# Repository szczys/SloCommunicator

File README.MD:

SloCommunicator
======

Communicator watch built for 2016 Bring-a-Hack (end of Bay Area Maker Faire Weekend).

This is based on the stalled [SloJak](https://github.com/szczys/SloJak) project. It is a 128x64 OLED screen with a rotary encoder and two buttons (actually 3 with encoder click but that's not designed into the board artwork).

Two things prevent this watch from communicating: I would need a second one to communicate with, and I didn't include the 900 MHz radio module in the design. This is just a quick and dirty built.

To make up for the lack of actual communications I will write KnobSnake, a classic game of snake that's played only by spinning the rotary encoder knob.

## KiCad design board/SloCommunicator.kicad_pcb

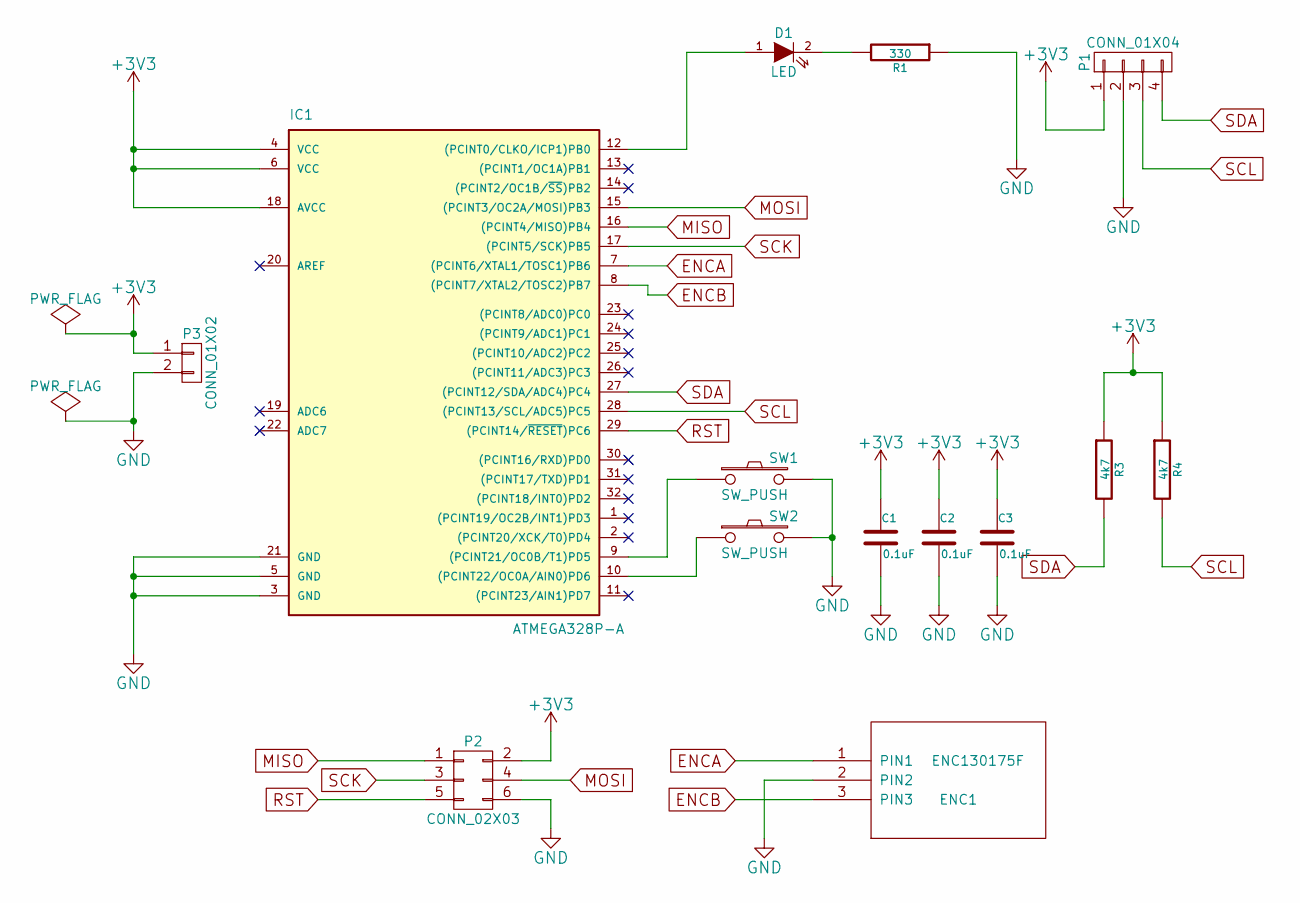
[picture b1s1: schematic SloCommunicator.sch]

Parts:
C1, C2, C3: 0.1uF; C_0805
D1: LED; LED_0805
ENC1: ENC130175F; enc130175f
IC1: ATMEGA328P-A; TQFP-32_7x7mm_Pitch0.8mm
P1: CONN_01X04; Pin_Header_Straight_1x04
P2: CONN_02X03; Pin_Header_Straight_2x03
P3: CONN_01X02; Pin_Header_Straight_1x02
R1: 330; R_0805
R3, R4: 4k7; R_0805
SW1, SW2: SW_PUSH; TACT_SMALL

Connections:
+3V3: C1.1, C2.1, C3.1, IC1.4 (VCC), IC1.6 (VCC), IC1.18 (AVCC), P1.1, P2.2, P3.1, R3.1, R4.1
ENCA: ENC1.1 (PIN1), IC1.7 ((PCINT6/XTAL1/TOSC1)PB6)
ENCB: ENC1.3 (PIN3), IC1.8 ((PCINT7/XTAL2/TOSC2)PB7)
GND: C1.2, C2.2, C3.2, ENC1.2 (PIN2), IC1.3 (GND), IC1.5 (GND), IC1.21 (GND), P1.2, P2.6, P3.2, R1.1, SW1.2, SW2.2
MISO: IC1.16 ((PCINT4/MISO)PB4), P2.1
MOSI: IC1.15 ((PCINT3/OC2A/MOSI)PB3), P2.4
unnamed: D1.1 (A), IC1.12 ((PCINT0/CLKO/ICP1)PB0)
unnamed: D1.2 (K), R1.2
unnamed: IC1.9 ((PCINT21/OC0B/T1)PD5), SW1.1
unnamed: IC1.10 ((PCINT22/OC0A/AIN0)PD6), SW2.1
RST: IC1.29 ((PCINT14/~RESET~)PC6), P2.5
SCK: IC1.17 ((PCINT5/SCK)PB5), P2.3
SCL: IC1.28 ((PCINT13/SCL/ADC5)PC5), P1.3, R4.2
SDA: IC1.27 ((PCINT12/SDA/ADC4)PC4), P1.4, R3.2

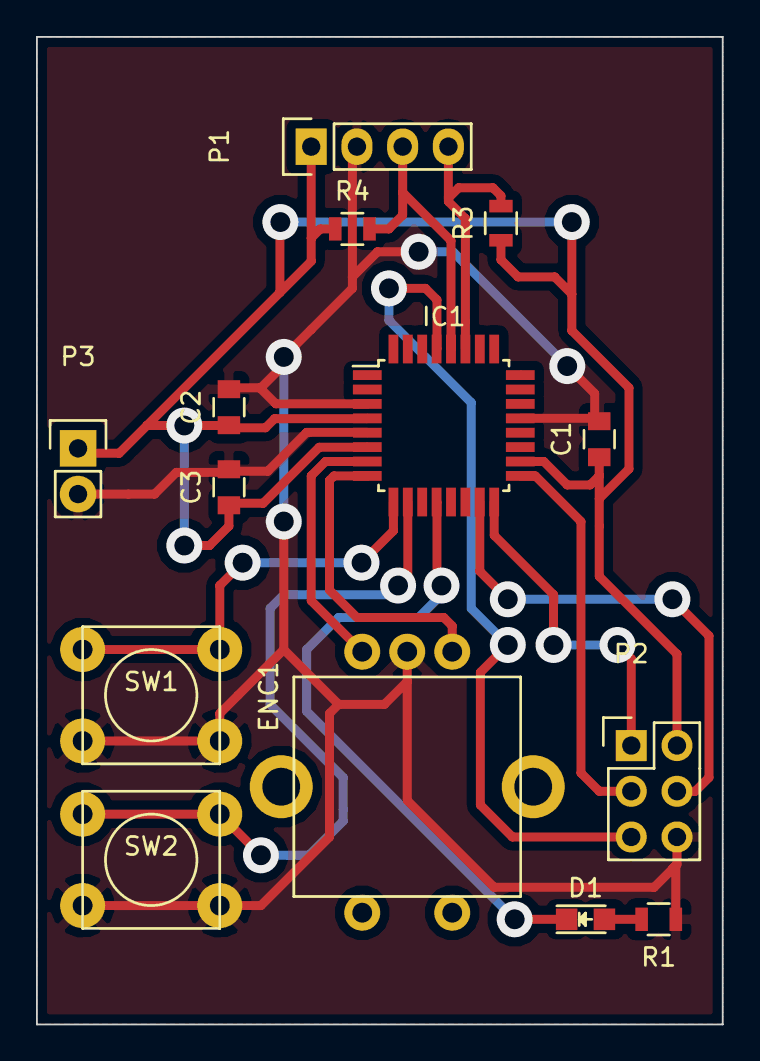
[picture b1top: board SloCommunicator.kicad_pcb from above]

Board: 2 copper layers, 38.1 x 54.9 mm, 14 parts (0 on the bottom side), 14 nets.

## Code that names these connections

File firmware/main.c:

/********************************
* SloJak                    	*
* MIT License               	*
* Copyright 2015 - Mike Szczys  *
* http://jumptuck.com 	    	*
*				                *
********************************/

#define F_CPU 8000000

#include <avr/io.h>
#include <avr/interrupt.h>
#include <avr/pgmspace.h>
#include <util/delay.h>

#include "menu.h"
#include "oledControl.h"
#include "game.h"


/************** Setup a rotary encoder ********************/
/* Atmega168 */
/* encoder port */
#define ENC_CTL	DDRB	//encoder port control
#define ENC_WR	PORTB	//encoder port write
#define ENC_RD	PINB	//encoder port read
#define ENC_A 6
#define ENC_B 7

volatile int8_t knobChange = 0;

/************** Setup input buttons *********************/
#define BUT_DDR     DDRD
#define BUT_PORT    PORTD
#define BUT_PIN     PIND
#define BUT_LEFT    (1<<PD5)
#define BUT_SEL     (1<<PD6)
#define BUT_MSK     (BUT_LEFT | BUT_SEL)

//Debounce
unsigned char debounce_cnt = 0;
volatile unsigned char key_press;
unsigned char key_state;

uint8_t goLeft = 0;
uint8_t goSel = 0;

uint8_t message[140] = "HELLOWORLDHELLOWORLDHELLOWORLDHELLOWORLDHELLOWORLDHELLOWORLDHELLOWORLD\0";

/**************** Prototypes *************************************/
unsigned char get_key_press(unsigned char key_mask);
void init_IO(void);
void init_interrupts(void);
int main(void);
/**************** End Prototypes *********************************/

/*********************
* Debounce Functions *
*********************/

unsigned char get_key_press(unsigned char key_mask)
{
  cli();               // read and clear atomic !
  key_mask &= key_press;                        // read key(s)
  key_press ^= key_mask;                        // clear key(s)
  sei();
  return key_mask;
}

void init_IO(void){
    //Rotary Encoder
    ENC_CTL &= ~(1<<ENC_A | 1<<ENC_B);
    ENC_WR |= 1<<ENC_A | 1<<ENC_B;

    //Buttons
    BUT_DDR &= ~(BUT_LEFT | BUT_SEL);      //Set as input
    BUT_PORT |= BUT_LEFT | BUT_SEL;      //Enable pull-up
}

void init_interrupts(void) {
    //Pin change interrupts for the rotary encoder
    PCICR |= 1<<PCIE0;      //enable PCINT0_vect  (PCINT0..7 pins)
    PCMSK0 |= 1<<PCINT6;    //interrupt on PCINT6 pin
    PCMSK0 |= 1<<PCINT7;    //interrupt on PCINT7 pin

    //Timer overflow for debounce and systick
    TCCR0B |= 1<<CS02 | 1<<CS00;		//Divide by 1024
    TIMSK0 |= 1<<TOIE0;			//enable timer overflow interrupt

    sei();
}

int main(void)
{
    init_IO();
    init_interrupts();
    oledInit();
    _delay_ms(200);

    oledSetCursor(cursX, cursY);
    putChar(66,1);
    advanceCursor(6);

    compose();

    initMenu();

    while(1)
    {
        if (get_key_press(BUT_SEL))
        {
            //Lookup and execute action
            doSelect[optionIndex]();
        }

        if (get_key_press(BUT_LEFT))
        {
            doBack();
        }

        if (knobChange) {
            if (knobChange > 0) {
                knobLeft();
            }
            else {
                knobRight();
            }
            knobChange = 0;
        }
        
        if (game_running && move_tick) {
            serviceGame();
            move_tick = 0;
        }
    }
}

ISR(PCINT0_vect) {
    /* Encoder service code is from Circuits@Home */
    /* https://www.circuitsathome.com/mcu/rotary-encoder-interrupt-service-routine-for-avr-micros */

    static uint8_t old_AB = 3;  //lookup table index
    static int8_t encval = 0;   //encoder value
    static const int8_t enc_states [] PROGMEM = {0,-1,1,0,1,0,0,-1,-1,0,0,1,0,1,-1,0};  //encoder lookup table

    old_AB <<=2;  //remember previous state
    old_AB |= ((ENC_RD>>6) & 0x03 ); //Shift magic to get PB6 and PB7 to LSB
    encval += pgm_read_byte(&(enc_states[( old_AB & 0x0f )]));
    /* post "Navigation forward/reverse" event */
    if( encval < -3 ) {  //four steps forward
        knobChange = -1;
        encval = 0;
    }
    else if( encval > 3  ) {  //four steps backwards
        knobChange = 1;
        encval = 0;
    }
}

ISR(TIMER0_OVF_vect) {
    static unsigned char ct0, ct1;
    unsigned char i;

    TCNT0 = (unsigned char)(signed short)-(F_CPU / 1024 * 10e-3 + 0.5);   // preload for 10ms

    i = key_state ^ ~BUT_PIN;    // key changed ?
    ct0 = ~( ct0 & i );          // reset or count ct0
    ct1 = ct0 ^ (ct1 & i);       // reset or count ct1
    i &= ct0 & ct1;              // count until roll over ?
    key_state ^= i;              // then toggle debounced state
    key_press |= key_state & i;  // 0->1: key press detect
    
    static uint8_t delayCount = STD_DELAY/10;   //This is a red herring. delayCount should be exposed to game.c
    
    if (++timingDelay >= delayCount) {
        timingDelay = 0;
        ++move_tick;
    }
}

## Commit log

2016-05-14 Add picture
2016-05-14 Added button debounce; cleaned up
2016-05-14 Added game option to homescreen
2016-05-14 Added game option Added ability to set pixel (FIXME ready byte locaiton from display first so we don't overwrite)
2016-05-14 Display data cannot be read with this particular screen (setting individual pixels must be done using a memory buffer)
2016-05-14 Implemented buffer for game
2016-05-14 Pulling in snake code
2016-05-17 Knob now controls the snake
2016-05-17 Added Game Over message
2016-05-17 abstracted exit game function
2016-05-17 Abstracted game start and restart
2016-05-17 Implemented random fruit generation
